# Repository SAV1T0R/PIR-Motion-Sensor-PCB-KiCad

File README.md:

• **PIR Motion Sensor PCB**

Designed a Passive Infrared (PIR) Motion Sensor printed circuit board (PCB) using KiCad. This project includes schematic capture, PCB layout design, Gerber file generation, and a Bill of Materials (BOM) for manufacturing. The design demonstrates the complete PCB development workflow from circuit design to fabrication-ready outputs.

---

• **Features**

- Designed the complete PIR motion sensor schematic in KiCad.
- Created the PCB layout with proper component placement and routing.
- Generated Gerber and drill files for PCB fabrication.
- Generated a Bill of Materials (BOM).
- Performed Electrical Rules Check (ERC) and Design Rules Check (DRC).

---

• **Software Used**

- KiCad 9
- ERC (Electrical Rules Check)
- DRC (Design Rules Check)

---

• **Project Files**

- KiCad project (.kicad_pro)
- Schematic (.kicad_sch)
- PCB layout (.kicad_pcb)
- Gerber files
- Drill files
- Bill of Materials (BOM)
- Project images

---

• **Applications**

- Motion Detection
- Home Security Systems
- Smart Lighting
- Occupancy Detection
- Home Automation

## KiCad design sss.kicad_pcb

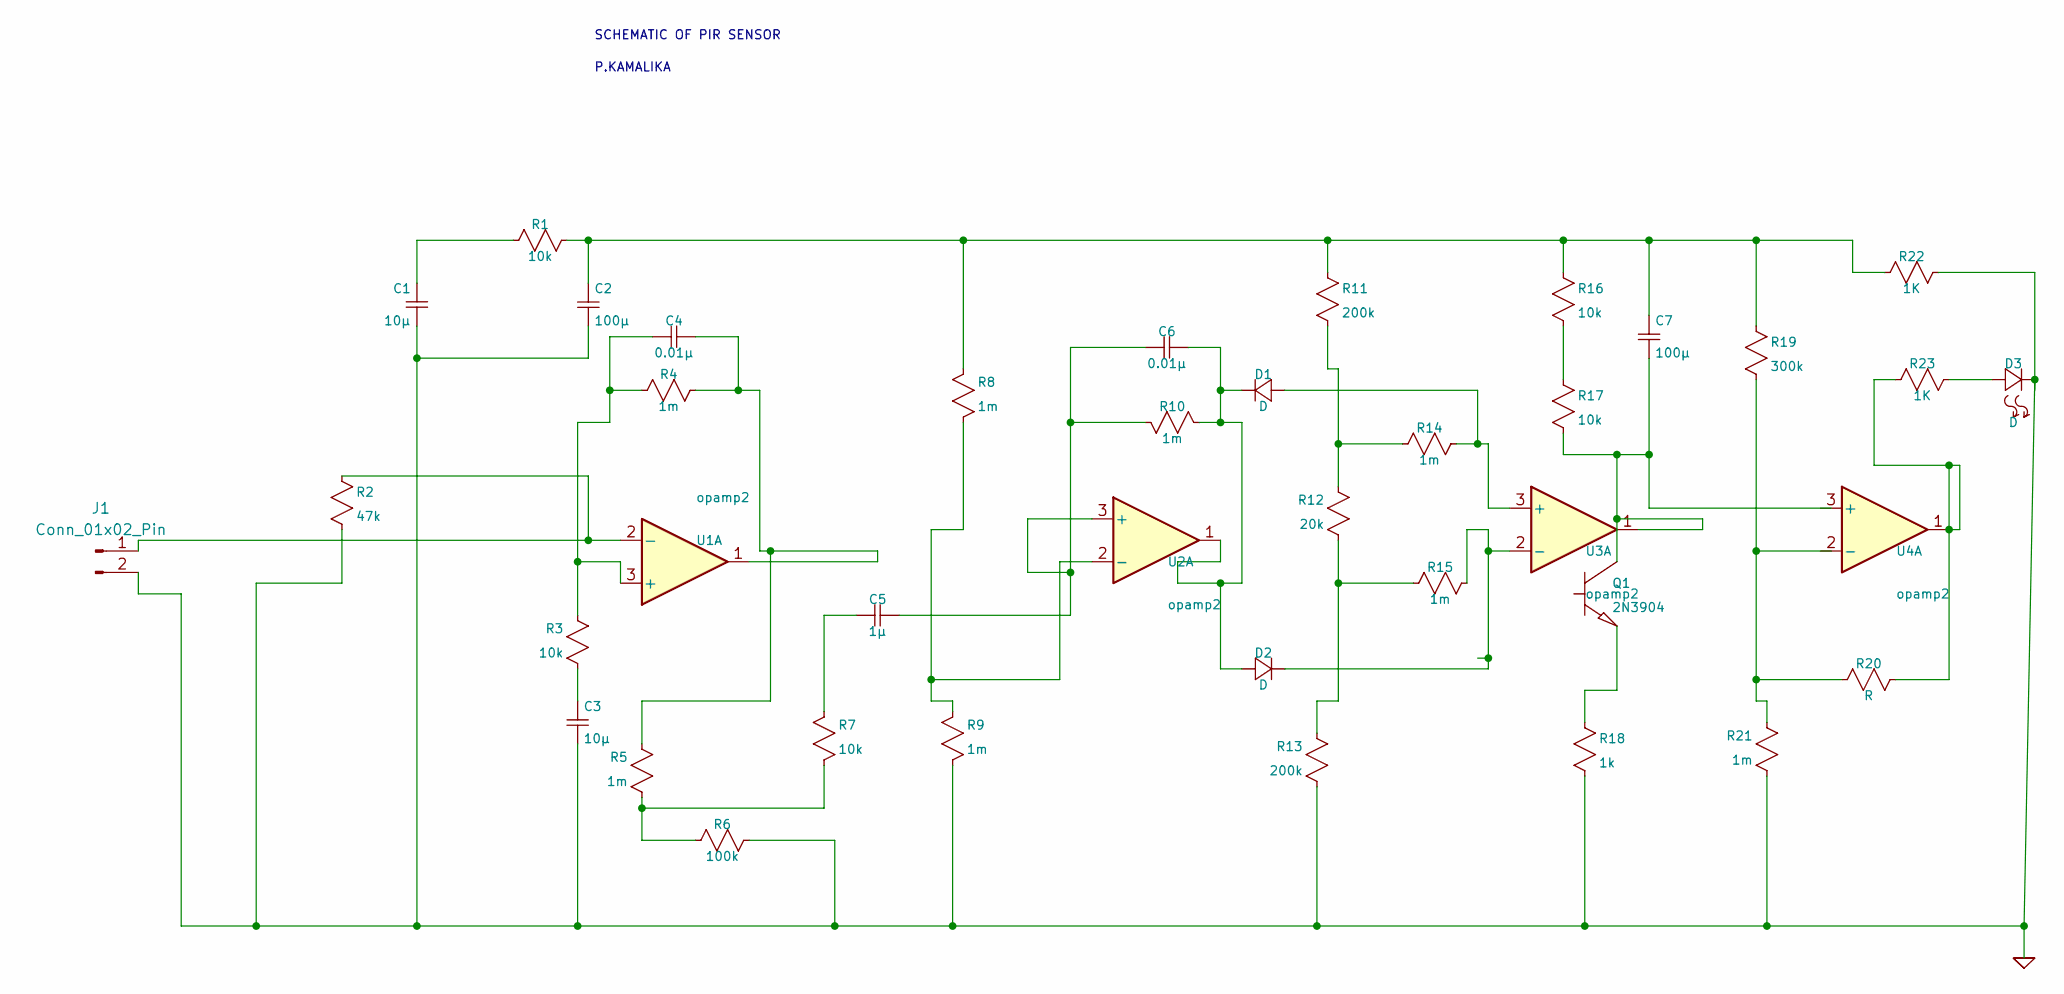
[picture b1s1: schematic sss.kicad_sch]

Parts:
C1, C3: 10μ; C_Disc_D5.0mm_W2.5mm_P5.00mm
C2, C7: 100μ; C_Disc_D5.0mm_W2.5mm_P5.00mm
C4, C6: 0.01μ; C_Disc_D5.0mm_W2.5mm_P5.00mm
C5: 1μ; C_Disc_D5.0mm_W2.5mm_P5.00mm
D1, D2, D3: D; D_DO-35_SOD27_P7.62mm_Horizontal
J1: Conn_01x02_Pin; PinHeader_1x02_P2.54mm_Vertical
Q1: 2N3904; TO-92_Inline
R1, R3, R7, R16, R17: 10k; R_Axial_DIN0207_L6.3mm_D2.5mm_P7.62mm_Horizontal
R2: 47k; R_Axial_DIN0207_L6.3mm_D2.5mm_P7.62mm_Horizontal
R4, R5, R8, R9, R10, R14, R15, R21: 1m; R_Axial_DIN0207_L6.3mm_D2.5mm_P7.62mm_Horizontal
R6: 100k; R_Axial_DIN0207_L6.3mm_D2.5mm_P7.62mm_Horizontal
R11, R13: 200k; R_Axial_DIN0207_L6.3mm_D2.5mm_P7.62mm_Horizontal
R12: 20k; R_Axial_DIN0207_L6.3mm_D2.5mm_P7.62mm_Horizontal
R18: 1k; R_Axial_DIN0207_L6.3mm_D2.5mm_P7.62mm_Horizontal
R19: 300k; R_Axial_DIN0207_L6.3mm_D2.5mm_P7.62mm_Horizontal
R20: R; R_Axial_DIN0207_L6.3mm_D2.5mm_P7.62mm_Horizontal
R22, R23: 1K; R_Axial_DIN0207_L6.3mm_D2.5mm_P7.62mm_Horizontal
U1, U2, U3, U4: opamp2; DIP-14_W7.62mm

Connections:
0: C1.1, C2.2, C3.2, D3.2 (-), J1.2, R2.2, R6.2, R9.1, R13.1, R18.2, R21.1, R22.2
unnamed: C1.2, R1.2
unnamed: C2.1, C7.1, R1.1, R8.2, R11.1, R16.1, R19.1, R22.1
unnamed: C3.1, R3.1
unnamed: C4.1, R4.1, R5.2, U1.1
unnamed: C5.2, R7.2
unnamed: D1.1 (+), R14.2, U3.3 (+)
unnamed: C6.1, D1.2 (-), D2.1 (+), R10.1, U2.1
unnamed: D2.2 (-), R15.2, U3.2 (-)
unnamed: D3.1 (+), R23.1
unnamed: J1.1, R2.1, U1.2 (-)
unnamed: C7.2, Q1.1 (C), R17.2, U3.1
unnamed: Q1.3 (E), R18.1
unnamed: R5.1, R6.1, R7.1
unnamed: R11.2, R12.2, R14.1
unnamed: R12.1, R13.2, R15.1
unnamed: R16.2, R17.1
unnamed: R19.2, R20.2, R21.2
unnamed: R20.1, R23.2, U4.1
unnamed: C4.2, R3.2, R4.2, U1.3 (+)
unnamed: C5.1, C6.2, R10.2, U2.3 (+)
unnamed: R8.1, R9.2, U2.2 (-)

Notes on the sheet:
SCHEMATIC OF PIR SENSOR
P.KAMALIKA

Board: 2 copper layers, 39 parts (0 on the bottom side), 22 nets, no tracks yet.
